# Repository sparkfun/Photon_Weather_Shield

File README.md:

⛔️ Discontinued
====================
*This product has been retired from our catalog.*

SparkFun_Photon_Weather_Shield
===========================

[*Photon Weather Shield (DEV-13630 )*](https://www.sparkfun.com/products/13630)

The SparkFun Photon Weather Shield is an easy to use add-on board for the Photon form Particle.io, which  grants you access to barometric pressure, relative humidity, and temperature. There are also connections on this shield to optional sensors such as wind speed, direction, rain gauge and soil readings!

Repository Contents
-------------------

* **/Firmware** - Necessary libraies and example sketches to use the weather shield. 
* **/Hardware** - All Eagle design files (.brd, .sch)
* **/Production** - Test bed files and production panel files

Documentation
--------------
* **[Hookup Guide](https://learn.sparkfun.com/tutorials/photon-weather-shield-hookup-guide)** - Complete hookup guide for the Photon Wetaher Shield.
* **[SparkFun Fritzing repo](https://github.com/sparkfun/Fritzing_Parts)** - Fritzing diagrams for SparkFun products.
* **[SparkFun 3D Model repo](https://github.com/sparkfun/3D_Models)** - 3D models of SparkFun products. 

Product Versions
----------------
* [DEV-13630](https://www.sparkfun.com/products/13630)- Hardware version 1.0

Version History
---------------

License Information
-------------------

This product is _**open source**_! 

Please review the LICENSE.md file for license information. 

If you have any questions or concerns on licensing, please contact techsupport@sparkfun.com.

Distributed as-is; no warranty is given.

- Your friends at SparkFun.

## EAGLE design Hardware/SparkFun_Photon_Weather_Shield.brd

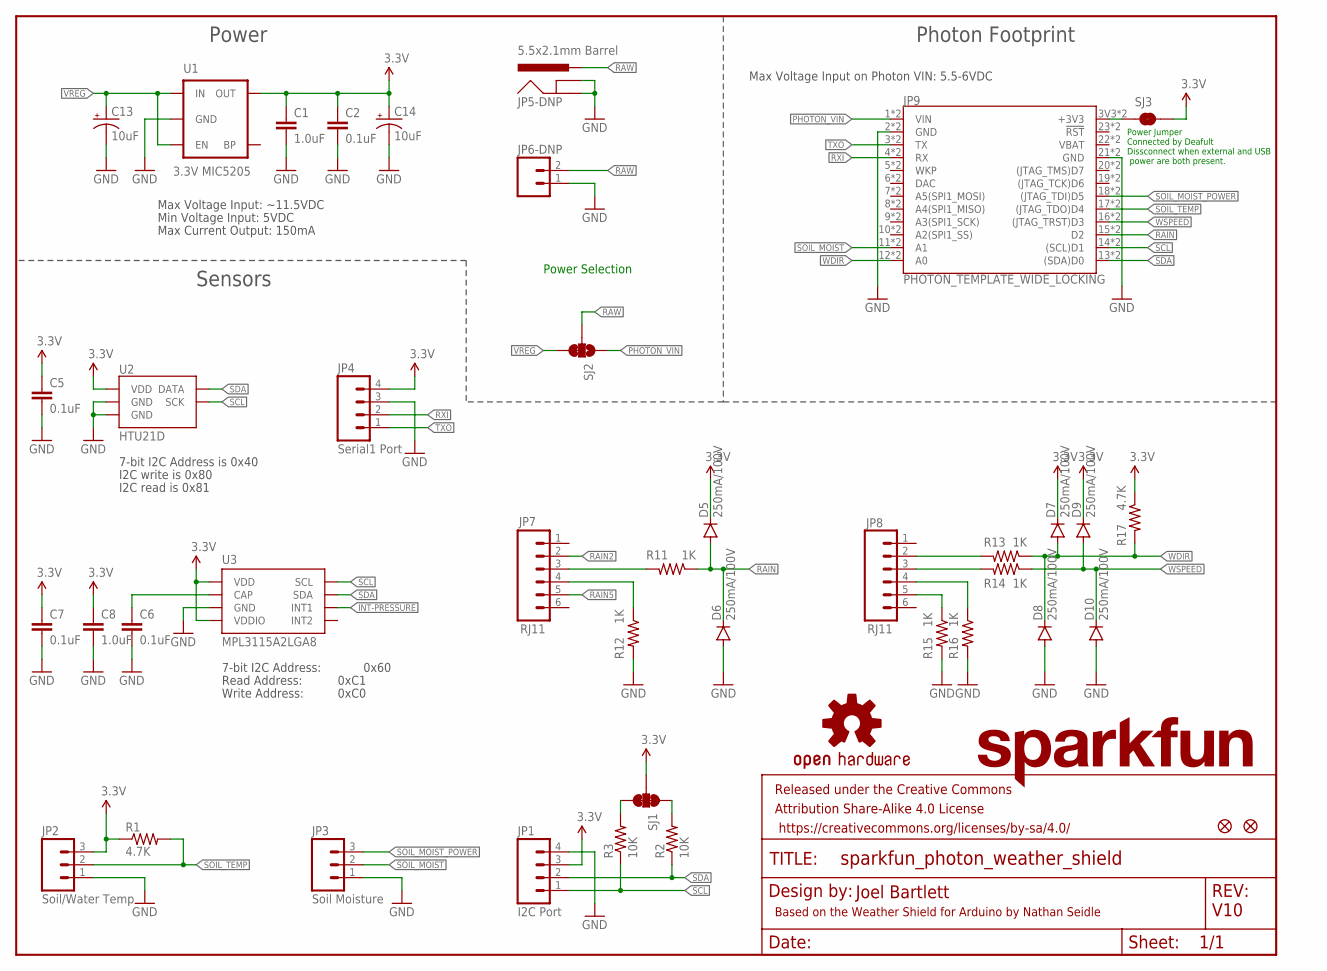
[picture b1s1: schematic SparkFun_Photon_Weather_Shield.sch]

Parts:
C1, C8: 1.0uF; 0603-CAP
C2, C5, C6, C7: 0.1uF; 0603-CAP
C13, C14: 10uF; EIA3216
D5, D6, D7, D8, D9, D10: 250mA/100V; SOD-323
FID1, FID2: FIDUCIAL1X2; FIDUCIAL-1X2
FRAME1: FRAME-LETTER; CREATIVE_COMMONS
JP1: I2C Port; 1X04
JP2: Soil/Water Temp; 1X03
JP3: Soil Moisture; 1X03
JP4: Serial1 Port; 1X04
JP5-DNP: 5.5x2.1mm Barrel; POWER_JACK_SMD
JP6-DNP: M023.5MM; SCREWTERMINAL-3.5MM-2
JP7, JP8: RJ11; RJ11-6
JP9: PHOTON_TEMPLATE_WIDE_LOCKING; SPARK_PHOTON_TEMPLATE_WIDE_LOCKING
LOGO1: OSHW-LOGOM; OSHW-LOGO-M
LOGO2: SFE_LOGO_NAME.1_INCH; SFE_LOGO_NAME_.1
R1, R17: 4.7K; 0603-RES
R2, R3: 10K; 0603-RES
R11, R12, R13, R14, R15, R16: 1K; 0603-RES
SJ1: JUMPER-PAD-3-NC_BY_TRACE; PAD-JUMPER-3-3OF3_NC_BY_TRACE_YES_SILK_FULL_BOX
SJ2: JUMPER-PAD-3-2OF3_NC_BY_TRACE_SMALL; PAD-JUMPER-3-2OF3_NC_BY_TRACE_YES_SILK_FULL_BOX
SJ3: JUMPER-PAD-2-NC_BY_TRACE; PAD-JUMPER-2-NC_BY_TRACE_YES_SILK
U1: 3.3V MIC5205; SOT23-5
U2: HTU21D
U3: MPL3115A2LGA8; LGA8

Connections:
3.3V: C1.1, C2.1, C5.1, C7.1, C8.1, C14.A (+), D5.C, D7.C, D9.C, JP1.3, JP2.3, JP4.4, R1.1, R17.1, SJ1.2, SJ3.2, U1.5 (OUT), U2.VDD, U3.1 (VDD), U3.4 (VDDIO)
GND: C1.2, C2.2, C5.2, C6.2, C7.2, C8.2, C13.C (-), C14.C (-), D6.A, D8.A, D10.A, JP1.4, JP2.1, JP3.1, JP4.3, JP5-DNP.GND (GNDBREAK), JP5-DNP.P$4 (GND), JP6-DNP.1, JP9.2 (GND), JP9.21 (GND), JP9.GND@0 (GND), JP9.GND@2 (GND), R12.2, R15.2, R16.2, U1.2 (GND), U2.7 (GND), U2.GND, U3.3 (GND)
INT-PRESSURE: U3.6 (INT1)
unnamed: JP8.3, R14.2
unnamed: JP8.2, R13.2
unnamed: R3.2, SJ1.3
unnamed: JP7.3, R11.2
unnamed: C6.1, U3.2 (CAP)
unnamed: R2.2, SJ1.1
unnamed: JP9.3V3 (+3V3), JP9.24 (+3V3), SJ3.1
unnamed: JP7.4, R12.1
unnamed: JP8.5, R15.1
unnamed: JP8.4, R16.1
PHOTON_VIN: JP9.1 (VIN), JP9.VIN, SJ2.1
RAIN: D5.A, D6.C, JP9.15 (D2), JP9.D2, R11.1
RAIN2: JP7.2
RAIN5: JP7.5
RAW: JP5-DNP.VIN0 (PWR), JP6-DNP.2, SJ2.2
RXI: JP4.2, JP9.4 (RX), JP9.RX
SCL: JP1.1, JP9.14 ((SCL)D1), JP9.D1 ((SCL)D1), R3.1, U2.SCK, U3.8 (SCL)
SDA: JP1.2, JP9.13 ((SDA)D0), JP9.D0 ((SDA)D0), R2.1, U2.DATA, U3.7 (SDA)
SOIL_MOIST: JP3.2, JP9.11 (A1), JP9.A1
SOIL_MOIST_POWER: JP3.3, JP9.18 ((JTAG_TDI)D5), JP9.D5 ((JTAG_TDI)D5)
SOIL_TEMP: JP2.2, JP9.17 ((JTAG_TDO)D4), JP9.D4 ((JTAG_TDO)D4), R1.2
TXO: JP4.1, JP9.3 (TX), JP9.TX
VREG: C13.A (+), SJ2.3, U1.1 (IN), U1.3 (EN)
WDIR: D7.A, D8.C, JP9.12 (A0), JP9.A0, R13.1, R17.2
WSPEED: D9.A, D10.C, JP9.16 ((JTAG_TRST)D3), JP9.D3 ((JTAG_TRST)D3), R14.1

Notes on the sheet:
Max Voltage Input: ~11.5VDC
Max Current Output: 150mA
Read Address:
Write Address:
7-bit I2C Address:
0x60
0xC1
0xC0
7-bit I2C Address is 0x40
I2C write is 0x80
I2C read is 0x81
Sensors
Power
Photon Footprint
Power Selection
Based on the Weather Shield for Arduino by Nathan Seidle
Min Voltage Input: 5VDC
Power Jumper Connected by Deafult Dissconnect when external and USB power are both present.
Joel Bartlett
V10
Max Voltage Input on Photon VIN: 5.5-6VDC

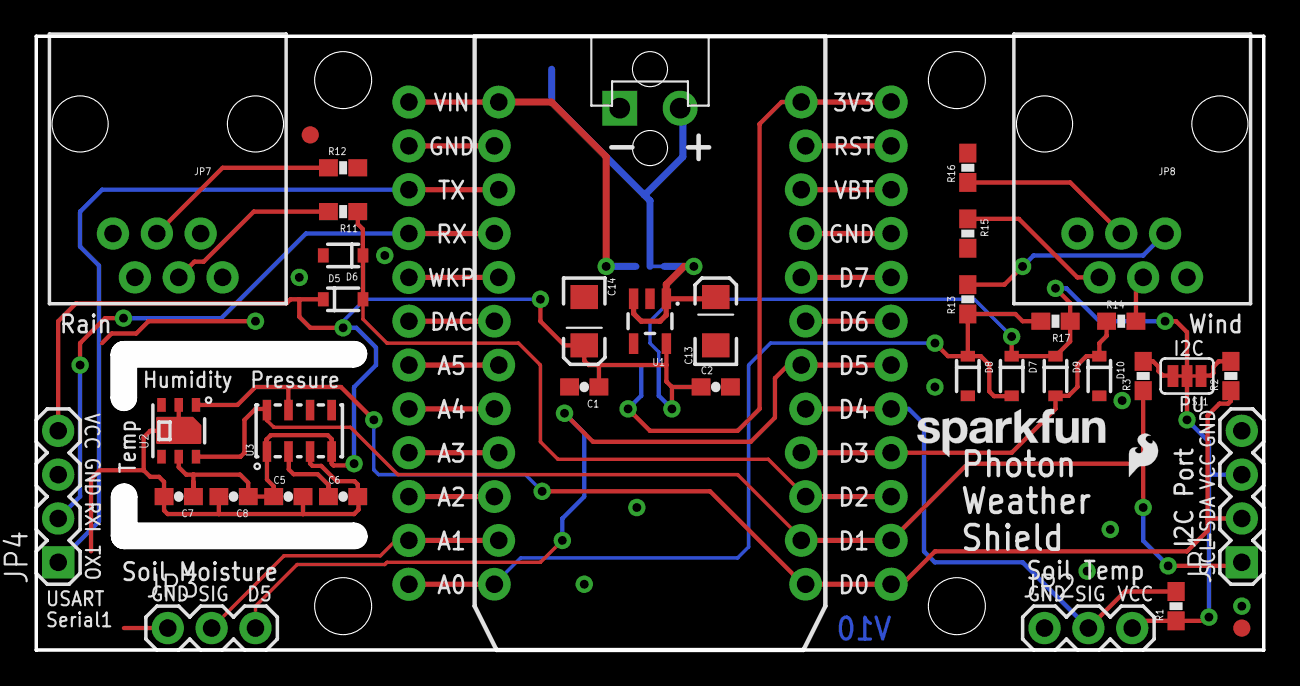
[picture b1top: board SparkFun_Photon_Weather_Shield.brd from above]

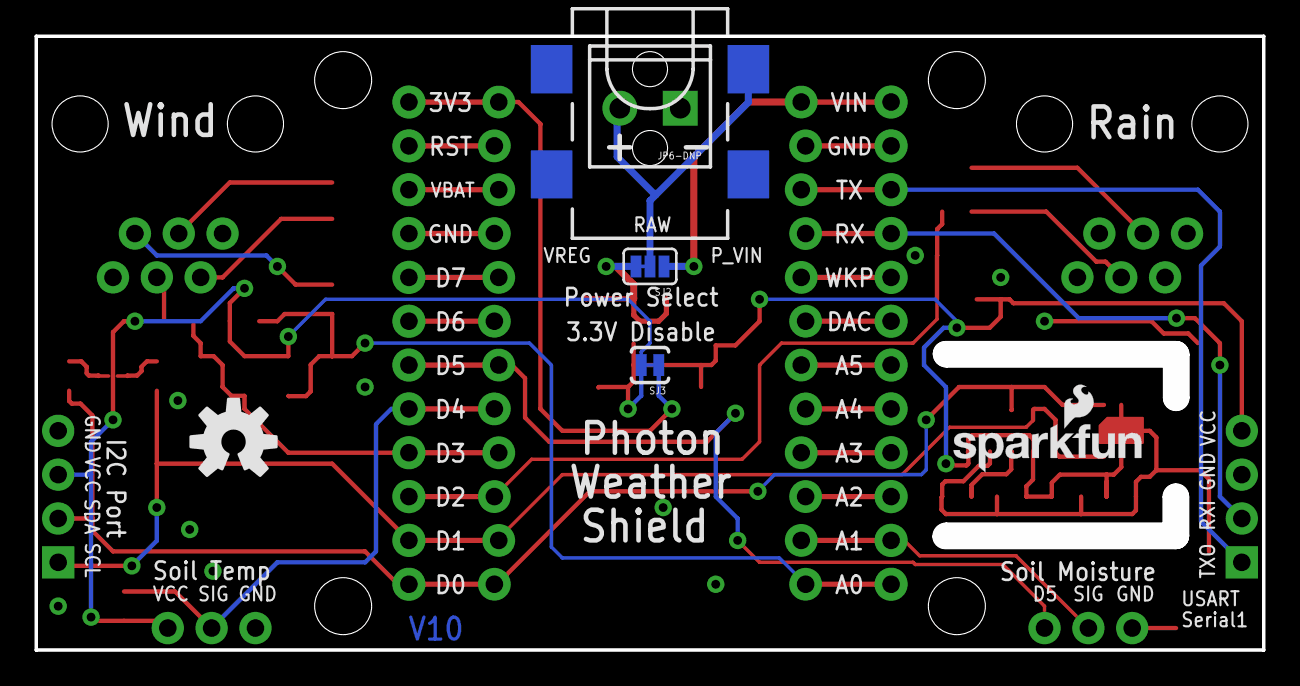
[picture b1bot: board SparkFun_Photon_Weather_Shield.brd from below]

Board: 2 copper layers, 69.8 x 34.2 mm, 46 parts (6 on the bottom side), 25 nets.

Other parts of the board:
U$1: SFE_LOGO_NAME_FLAME_.1
U$3: SFE_LOGO_FLAME_.1

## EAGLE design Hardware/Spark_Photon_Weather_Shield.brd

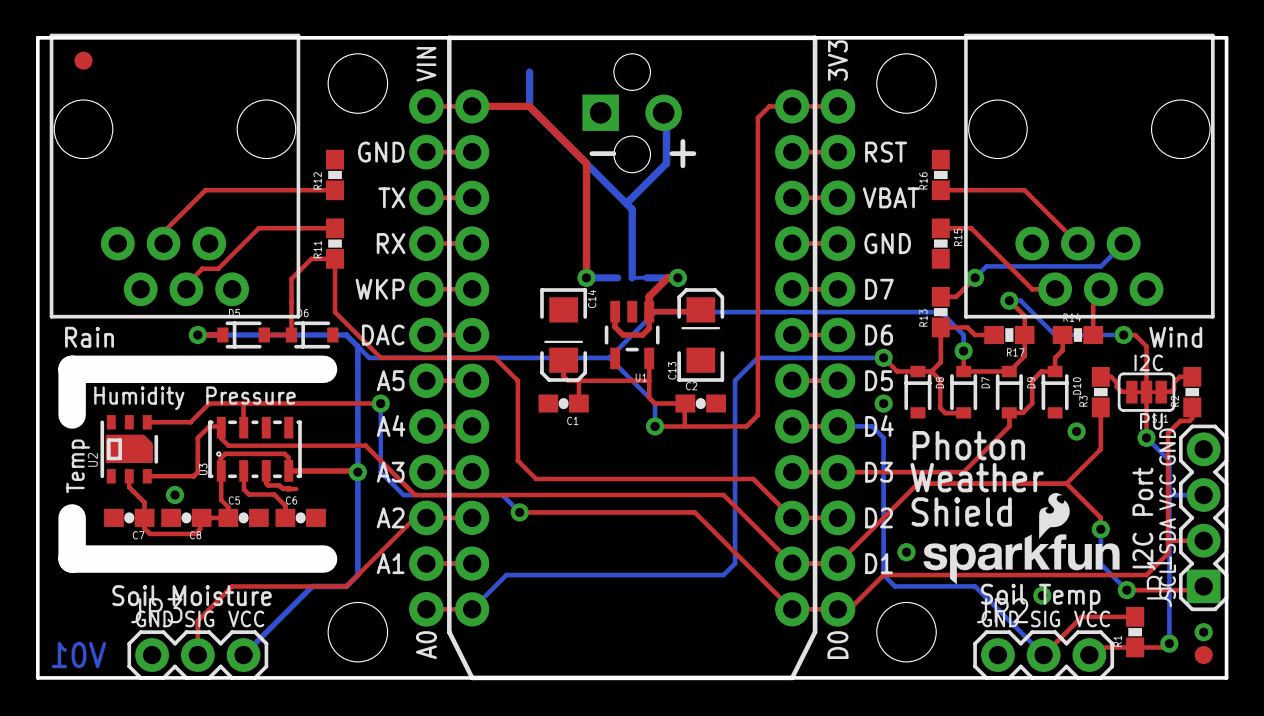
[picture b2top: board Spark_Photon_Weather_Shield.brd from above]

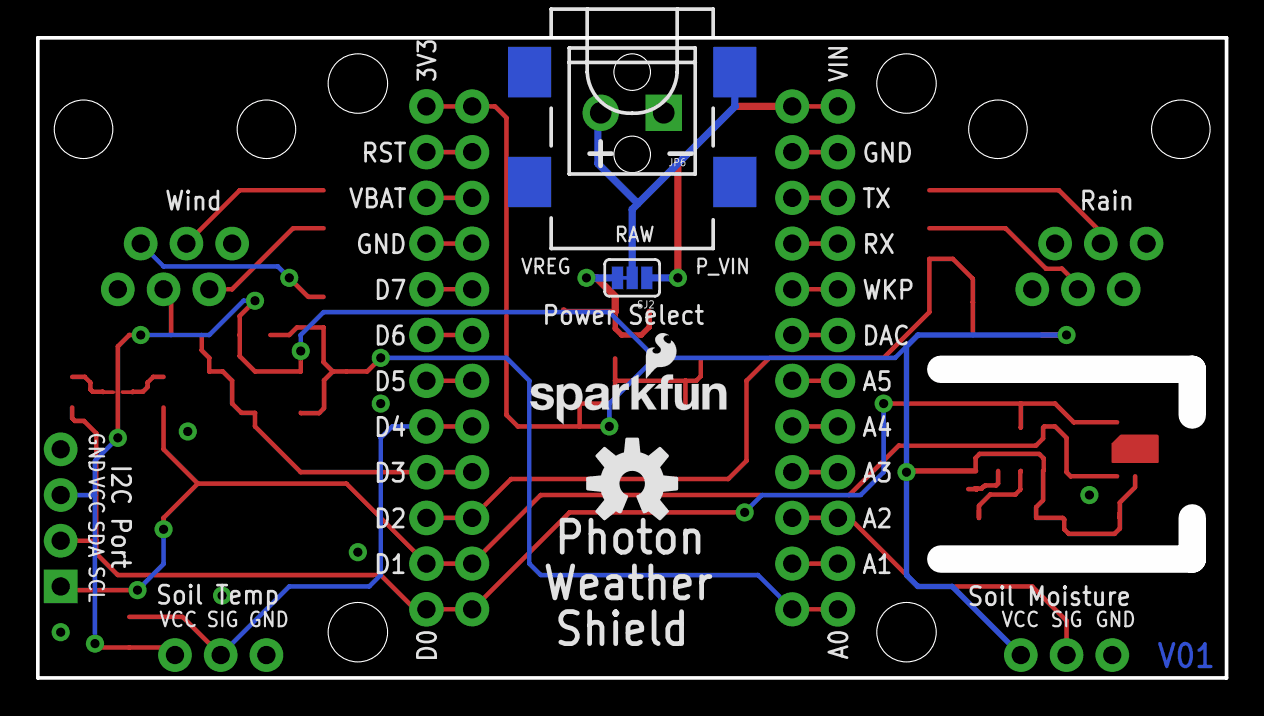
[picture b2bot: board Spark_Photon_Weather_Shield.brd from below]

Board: 2 copper layers, 64.7 x 34.2 mm, 43 parts (5 on the bottom side), 24 nets.

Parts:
C1, C8: 1uF; 0603-CAP
C2, C5, C6, C7: 0.1uF; 0603-CAP
C13, C14: 10uF; EIA3216
D5, D6, D7, D8, D9, D10: BAS16; SOD-323
FID1, FID2: FIDUCIAL1X2; FIDUCIAL-1X2
FRAME2: CREATIVE_COMMONS
JP1: 1X04
JP2, JP3: 1X03
JP4: SPARK_PHOTONTEMPLATE; SPARK_PHOTON_TEMPLATE
JP5: 5.5x2.1mm Barrel; POWER_JACK_SMD
JP6: M023.5MM; SCREWTERMINAL-3.5MM-2
JP7-DNP: RJ11-RAIN; RJ11-6
JP8-DNP: RJ11-WIND; RJ11-6
LOGO1: OSHW-LOGOM; OSHW-LOGO-M
LOGO2: SFE_LOGO_NAME_FLAME.1_INCH; SFE_LOGO_NAME_FLAME_.1
R1, R17: 4.7K; 0603-RES
R2, R3: 10K; 0603-RES
R11, R12, R13, R14, R15, R16: 1K; 0603-RES
SJ1: PAD-JUMPER-3-3OF3_NC_BY_TRACE_YES_SILK_FULL_BOX
SJ2: PAD-JUMPER-3-2OF3_NC_BY_TRACE_YES_SILK_FULL_BOX
U1: 3.3V MIC5219; SOT23-5
U2: HTU21D
U3: MPL3115A2LGA8; LGA8
U$1: SFE_LOGO_NAME_FLAME_.1

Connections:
3.3V: C1.1, C2.1, C5.1, C7.1, C8.1, C14.A, D5.1, D7.1, D9.1, JP1.3, JP2.3, JP3.3, JP4.3V3, JP4.24, R1.1, R17.1, SJ1.2, U1.5, U2.VDD, U3.1, U3.4
GND: C1.2, C2.2, C5.2, C6.2, C7.2, C8.2, C13.C, C14.C, D6.2, D8.2, D10.2, JP1.4, JP2.1, JP3.1, JP4.2, JP4.21, JP4.GND@0, JP4.GND@2, JP5.GND, JP5.P$4, JP6.1, R12.2, R15.2, R16.2, U1.2, U2.7, U2.GND, U3.3
LIGHT: JP4.11, JP4.A1
unnamed: JP8-DNP.3, R14.2
unnamed: JP8-DNP.2, R13.2
unnamed: R3.2, SJ1.3
unnamed: JP7-DNP.3, R11.2
unnamed: C6.1, U3.2
unnamed: R2.2, SJ1.1
unnamed: JP7-DNP.4, R12.1
unnamed: JP8-DNP.5, R15.1
unnamed: JP8-DNP.4, R16.1
PHOTON_VIN: JP4.1, JP4.VIN, SJ2.1
RAIN: D5.2, D6.1, JP4.15, JP4.D2, R11.1
RAW: JP5.VIN0, JP6.2, SJ2.2
RXI: JP4.4, JP4.RX
SCL: JP1.1, JP4.14, JP4.D1, R3.1, U2.SCK, U3.8
SDA: JP1.2, JP4.13, JP4.D0, R2.1, U2.DATA, U3.7
SOIL_MOIST: JP3.2, JP4.10, JP4.A2
SOIL_TEMP: JP2.2, JP4.17, JP4.D4, R1.2
TXO: JP4.3, JP4.TX
VREG: C13.A, SJ2.3, U1.1, U1.3
WDIR: D7.2, D8.1, JP4.12, JP4.A0, R13.1, R17.2
WSPEED: D9.2, D10.1, JP4.16, JP4.D3, R14.1

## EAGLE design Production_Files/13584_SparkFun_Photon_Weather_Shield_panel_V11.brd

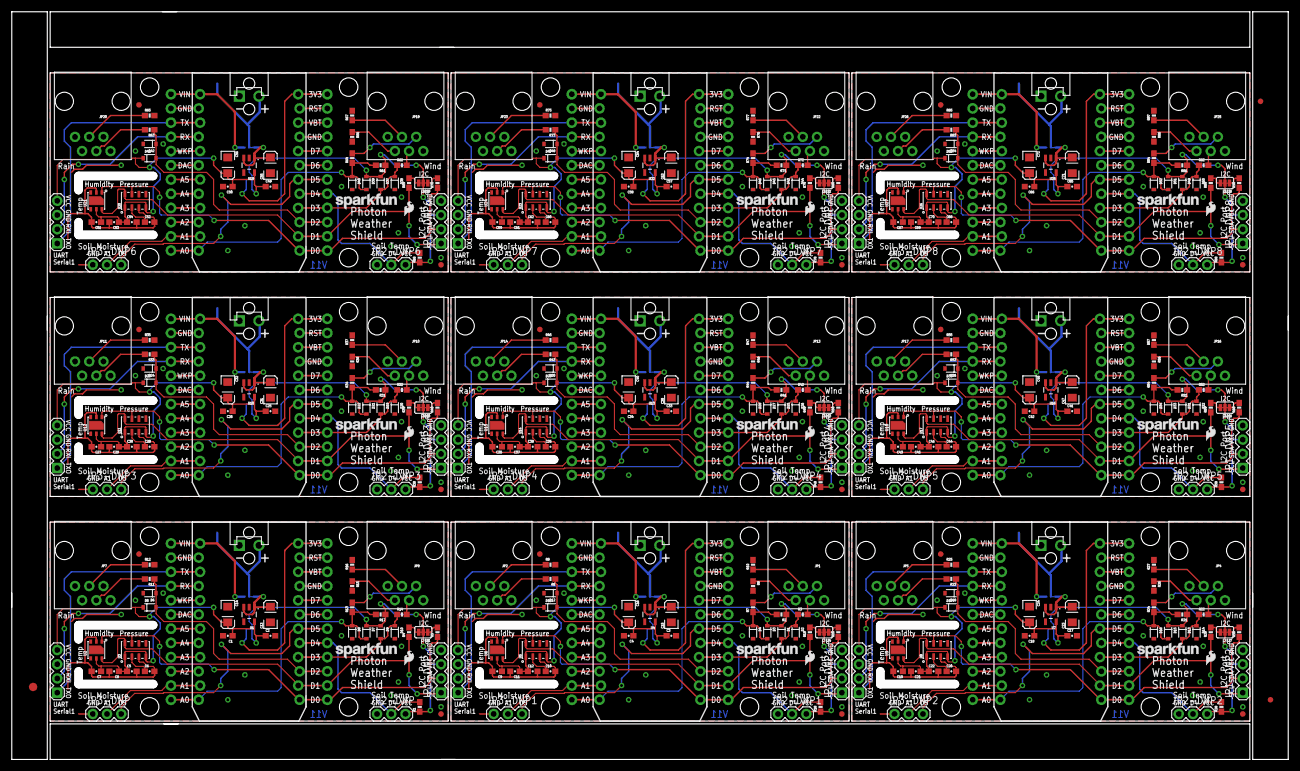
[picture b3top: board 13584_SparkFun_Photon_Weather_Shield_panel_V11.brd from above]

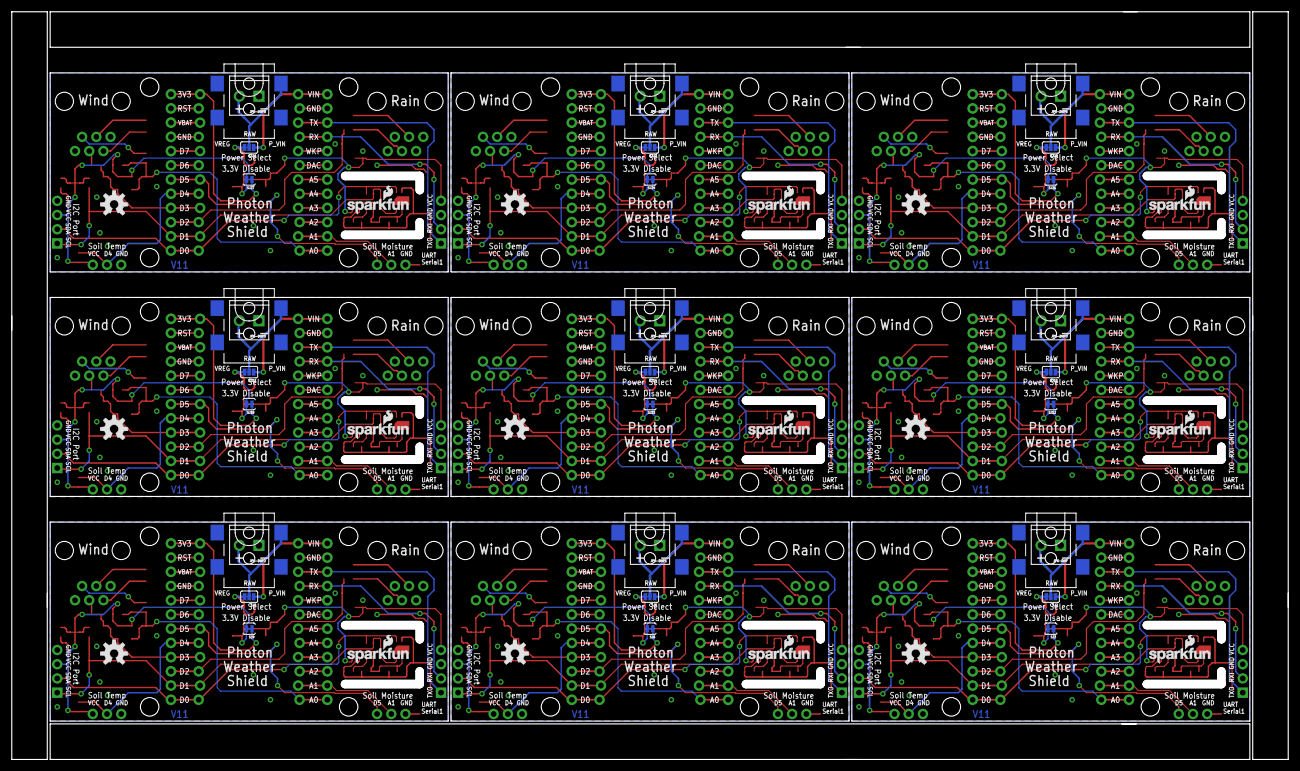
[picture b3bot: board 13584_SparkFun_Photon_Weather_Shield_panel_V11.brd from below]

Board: 2 copper layers, 226.8 x 132.3 mm, 408 parts (54 on the bottom side), 225 nets.

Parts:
C1, C4, C8, C11, C18, C21, C26, C29, C34, C37, C42, C45, C50, C53, C58, C61, C66, C69: 1.0uF; 0603-CAP
C2, C3, C5, C6, C7, C9, C10, C12, C17, C19, C20, C22, C25, C27, C28, C30, C33, C35, C36, C38, C41, C43, C44, C46, C49, C51, C52, C54, C57, C59, C60, C62, C65, C67, C68, C70: 0.1uF; 0603-CAP
C13, C14, C15, C16, C23, C24, C31, C32, C39, C40, C47, C48, C55, C56, C63, C64, C71, C72: 10uF; EIA3216
D1, D2, D3, D4, D5, D6, D7, D8, D9, D10, D11, D12, D13, D14, D15, D16, D17, D18, D19, D20, D21, D22, D23, D24, D25, D26, D27, D28, D29, D30, D31, D32, D33, D34, D35, D36, D37, D38, D39, D40, D41, D42, D43, D44, D45, D46, D47, D48, D49, D50, D51, D52, D53, D54: 250mA/100V; SOD-323
E$1: FIDUCIAL-1.5X3
E$7, E$8: FIDUCIAL-1X2
FID1, FID2, FID3, FID4, FID5, FID6, FID7, FID8, FID9, FID10, FID11, FID12, FID13, FID14, FID15, FID16, FID17, FID18: FIDUCIAL1X2; FIDUCIAL-1X2
JP1, JP2, JP4, JP5, JP7, JP8, JP10, JP11, JP13, JP14, JP16, JP17, JP19, JP20, JP22, JP23, JP25, JP26: RJ11; RJ11-6
JP1-DNP, JP1-DNP1, JP1-DNP2, JP1-DNP3, JP1-DNP4, JP1-DNP5, JP1-DNP6, JP1-DNP7, JP1-DNP8: I2C Port; 1X04
JP2-DNP, JP2-DNP1, JP2-DNP2, JP2-DNP3, JP2-DNP4, JP2-DNP5, JP2-DNP6, JP2-DNP7, JP2-DNP8: Soil/Water Temp; 1X03
JP3, JP6, JP9, JP12, JP15, JP18, JP21, JP24, JP27: PHOTON_TEMPLATE_WIDE_LOCKING; SPARK_PHOTON_TEMPLATE_WIDE_LOCKING
JP3-DNP, JP3-DNP1, JP3-DNP2, JP3-DNP3, JP3-DNP4, JP3-DNP5, JP3-DNP6, JP3-DNP7, JP3-DNP8: Soil Moisture; 1X03
JP4-DNP, JP4-DNP1, JP4-DNP2, JP4-DNP3, JP4-DNP4, JP4-DNP5, JP4-DNP6, JP4-DNP7, JP4-DNP8: Serial1 Port; 1X04
JP5-DNP, JP5-DNP1, JP5-DNP2, JP5-DNP3, JP5-DNP4, JP5-DNP5, JP5-DNP6, JP5-DNP7, JP5-DNP8: 5.5x2.1mm Barrel; POWER_JACK_SMD
JP6-DNP, JP6-DNP1, JP6-DNP2, JP6-DNP3, JP6-DNP4, JP6-DNP5, JP6-DNP6, JP6-DNP7, JP6-DNP8: SCREWTERMINAL-3.5MM-2
LOGO1, LOGO3, LOGO5, LOGO7, LOGO9, LOGO11, LOGO13, LOGO15, LOGO17: OSHW-LOGOM; OSHW-LOGO-M
LOGO2, LOGO4, LOGO6, LOGO8, LOGO10, LOGO12, LOGO14, LOGO16, LOGO18: SFE_LOGO_NAME.1_INCH; SFE_LOGO_NAME_.1
R1, R2, R4, R5, R17, R18, R19, R20, R21, R28, R29, R30, R31, R38, R39, R40, R41, R48, R49, R50, R51, R58, R59, R60, R61, R68, R69, R70, R71, R78, R79, R80, R81, R88, R89, R90: 4.7K; 0603-RES
R3, R6, R7, R8, R9, R10, R11, R12, R13, R14, R15, R16, R22, R23, R24, R25, R26, R27, R32, R33, R34, R35, R36, R37, R42, R43, R44, R45, R46, R47, R52, R53, R54, R55, R56, R57, R62, R63, R64, R65, R66, R67, R72, R73, R74, R75, R76, R77, R82, R83, R84, R85, R86, R87: 1K; 0603-RES
SJ1, SJ4, SJ7, SJ10, SJ13, SJ16, SJ19, SJ22, SJ25: PAD-JUMPER-3-3OF3_NC_BY_TRACE_YES_SILK_FULL_BOX
SJ2, SJ5, SJ8, SJ11, SJ14, SJ17, SJ20, SJ23, SJ26: PAD-JUMPER-3-2OF3_NC_BY_TRACE_YES_SILK_FULL_BOX
SJ3, SJ6, SJ9, SJ12, SJ15, SJ18, SJ21, SJ24, SJ27: PAD-JUMPER-2-NC_BY_TRACE_YES_SILK
U1, U4, U7, U10, U13, U16, U19, U22, U25: 3.3V MIC5219; SOT23-5
U2, U6, U9, U12, U15, U18, U21, U24, U27: SI7021
U3, U5, U8, U11, U14, U17, U20, U23, U26: MPL3115A2LGA8; LGA8
U$1, U$2, U$5, U$7, U$9, U$11, U$13, U$15, U$17: SFE_LOGO_NAME_FLAME_.1
U$3, U$4, U$6, U$8, U$10, U$12, U$14, U$16, U$18: SFE_LOGO_FLAME_.1

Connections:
3.3V: C1.1, C2.1, C5.1, C7.1, C8.1, C14.A, D5.C, D7.C, D9.C, JP1-DNP.3, JP2-DNP.3, JP4-DNP.4, R1.1, R17.1, SJ1.2, SJ3.2, U1.5, U2.VDD, U3.1, U3.4
3.3V1: C3.1, C4.1, C9.1, C11.1, C12.1, C16.A, D1.C, D3.C, D11.C, JP1-DNP1.3, JP2-DNP1.3, JP4-DNP1.4, R2.1, R18.1, SJ4.2, SJ6.2, U4.5, U5.1, U5.4, U6.VDD
3.3V2: C17.1, C18.1, C19.1, C21.1, C22.1, C24.A, D13.C, D15.C, D17.C, JP1-DNP2.3, JP2-DNP2.3, JP4-DNP2.4, R21.1, R28.1, SJ7.2, SJ9.2, U7.5, U8.1, U8.4, U9.VDD
3.3V3: C25.1, C26.1, C27.1, C29.1, C30.1, C32.A, D19.C, D21.C, D23.C, JP1-DNP3.3, JP2-DNP3.3, JP4-DNP3.4, R31.1, R38.1, SJ10.2, SJ12.2, U10.5, U11.1, U11.4, U12.VDD
3.3V4: C33.1, C34.1, C35.1, C37.1, C38.1, C40.A, D25.C, D27.C, D29.C, JP1-DNP4.3, JP2-DNP4.3, JP4-DNP4.4, R41.1, R48.1, SJ13.2, SJ15.2, U13.5, U14.1, U14.4, U15.VDD
3.3V5: C41.1, C42.1, C43.1, C45.1, C46.1, C48.A, D31.C, D33.C, D35.C, JP1-DNP5.3, JP2-DNP5.3, JP4-DNP5.4, R51.1, R58.1, SJ16.2, SJ18.2, U16.5, U17.1, U17.4, U18.VDD
3.3V6: C49.1, C50.1, C51.1, C53.1, C54.1, C56.A, D37.C, D39.C, D41.C, JP1-DNP6.3, JP2-DNP6.3, JP4-DNP6.4, R61.1, R68.1, SJ19.2, SJ21.2, U19.5, U20.1, U20.4, U21.VDD
3.3V7: C57.1, C58.1, C59.1, C61.1, C62.1, C64.A, D43.C, D45.C, D47.C, JP1-DNP7.3, JP2-DNP7.3, JP4-DNP7.4, R71.1, R78.1, SJ22.2, SJ24.2, U22.5, U23.1, U23.4, U24.VDD
3.3V8: C65.1, C66.1, C67.1, C69.1, C70.1, C72.A, D49.C, D51.C, D53.C, JP1-DNP8.3, JP2-DNP8.3, JP4-DNP8.4, R81.1, R88.1, SJ25.2, SJ27.2, U25.5, U26.1, U26.4, U27.VDD
GND: C1.2, C2.2, C5.2, C6.2, C7.2, C8.2, C13.C, C14.C, D6.A, D8.A, D10.A, JP1-DNP.4, JP2-DNP.1, JP3-DNP.1, JP4-DNP.3, JP5-DNP.GND, JP5-DNP.P$4, JP6-DNP.1, JP9.2, JP9.21, JP9.GND@0, JP9.GND@2, R12.2, R15.2, R16.2, U1.2, U2.GND, U3.3
GND1: C3.2, C4.2, C9.2, C10.2, C11.2, C12.2, C15.C, C16.C, D2.A, D4.A, D12.A, JP1-DNP1.4, JP2-DNP1.1, JP3.2, JP3.21, JP3.GND@0, JP3.GND@2, JP3-DNP1.1, JP4-DNP1.3, JP5-DNP1.GND, JP5-DNP1.P$4, JP6-DNP1.1, R8.2, R9.2, R10.2, U4.2, U5.3, U6.GND
GND2: C17.2, C18.2, C19.2, C20.2, C21.2, C22.2, C23.C, C24.C, D14.A, D16.A, D18.A, JP1-DNP2.4, JP2-DNP2.1, JP3-DNP2.1, JP4-DNP2.3, JP5-DNP2.GND, JP5-DNP2.P$4, JP6.2, JP6.21, JP6.GND@0, JP6.GND@2, JP6-DNP2.1, R25.2, R26.2, R27.2, U7.2, U8.3, U9.GND
GND3: C25.2, C26.2, C27.2, C28.2, C29.2, C30.2, C31.C, C32.C, D20.A, D22.A, D24.A, JP1-DNP3.4, JP2-DNP3.1, JP3-DNP3.1, JP4-DNP3.3, JP5-DNP3.GND, JP5-DNP3.P$4, JP6-DNP3.1, JP12.2, JP12.21, JP12.GND@0, JP12.GND@2, R35.2, R36.2, R37.2, U10.2, U11.3, U12.GND
GND4: C33.2, C34.2, C35.2, C36.2, C37.2, C38.2, C39.C, C40.C, D26.A, D28.A, D30.A, JP1-DNP4.4, JP2-DNP4.1, JP3-DNP4.1, JP4-DNP4.3, JP5-DNP4.GND, JP5-DNP4.P$4, JP6-DNP4.1, JP15.2, JP15.21, JP15.GND@0, JP15.GND@2, R45.2, R46.2, R47.2, U13.2, U14.3, U15.GND
GND5: C41.2, C42.2, C43.2, C44.2, C45.2, C46.2, C47.C, C48.C, D32.A, D34.A, D36.A, JP1-DNP5.4, JP2-DNP5.1, JP3-DNP5.1, JP4-DNP5.3, JP5-DNP5.GND, JP5-DNP5.P$4, JP6-DNP5.1, JP18.2, JP18.21, JP18.GND@0, JP18.GND@2, R55.2, R56.2, R57.2, U16.2, U17.3, U18.GND
GND6: C49.2, C50.2, C51.2, C52.2, C53.2, C54.2, C55.C, C56.C, D38.A, D40.A, D42.A, JP1-DNP6.4, JP2-DNP6.1, JP3-DNP6.1, JP4-DNP6.3, JP5-DNP6.GND, JP5-DNP6.P$4, JP6-DNP6.1, JP21.2, JP21.21, JP21.GND@0, JP21.GND@2, R65.2, R66.2, R67.2, U19.2, U20.3, U21.GND
GND7: C57.2, C58.2, C59.2, C60.2, C61.2, C62.2, C63.C, C64.C, D44.A, D46.A, D48.A, JP1-DNP7.4, JP2-DNP7.1, JP3-DNP7.1, JP4-DNP7.3, JP5-DNP7.GND, JP5-DNP7.P$4, JP6-DNP7.1, JP24.2, JP24.21, JP24.GND@0, JP24.GND@2, R75.2, R76.2, R77.2, U22.2, U23.3, U24.GND
GND8: C65.2, C66.2, C67.2, C68.2, C69.2, C70.2, C71.C, C72.C, D50.A, D52.A, D54.A, JP1-DNP8.4, JP2-DNP8.1, JP3-DNP8.1, JP4-DNP8.3, JP5-DNP8.GND, JP5-DNP8.P$4, JP6-DNP8.1, JP27.2, JP27.21, JP27.GND@0, JP27.GND@2, R85.2, R86.2, R87.2, U25.2, U26.3, U27.GND
unnamed: JP8.3, R14.2
unnamed: JP8.2, R13.2
unnamed: R4.2, SJ1.3
unnamed: JP7.3, R11.2
unnamed: C6.1, U3.2
unnamed: R5.2, SJ1.1
unnamed: JP9.3V3, JP9.24, SJ3.1
unnamed: C10.1, U5.2
unnamed: JP1.2, R7.2
unnamed: JP1.3, R3.2
unnamed: JP7.4, R12.1
unnamed: JP8.5, R15.1
unnamed: JP8.4, R16.1
unnamed: JP2.3, R6.2
unnamed: JP2.4, R8.1
unnamed: JP1.5, R9.1
unnamed: JP1.4, R10.1
unnamed: R19.2, SJ4.3
unnamed: R20.2, SJ4.1
unnamed: JP3.3V3, JP3.24, SJ6.1
unnamed: C20.1, U8.2
unnamed: JP4.2, R24.2
unnamed: JP4.3, R22.2
unnamed: JP5.3, R23.2
unnamed: JP5.4, R25.1
unnamed: JP4.5, R26.1
unnamed: JP4.4, R27.1
unnamed: R29.2, SJ7.3
unnamed: R30.2, SJ7.1
unnamed: JP6.3V3, JP6.24, SJ9.1
unnamed: C28.1, U11.2
unnamed: JP10.2, R34.2
unnamed: JP10.3, R32.2
unnamed: JP11.3, R33.2
unnamed: JP11.4, R35.1
unnamed: JP10.5, R36.1
unnamed: JP10.4, R37.1
unnamed: R39.2, SJ10.3
unnamed: R40.2, SJ10.1
unnamed: JP12.3V3, JP12.24, SJ12.1
unnamed: C36.1, U14.2
unnamed: JP13.2, R44.2
unnamed: JP13.3, R42.2
unnamed: JP14.3, R43.2
unnamed: JP14.4, R45.1
unnamed: JP13.5, R46.1
unnamed: JP13.4, R47.1
unnamed: R49.2, SJ13.3
unnamed: R50.2, SJ13.1
unnamed: JP15.3V3, JP15.24, SJ15.1
unnamed: C44.1, U17.2
unnamed: JP16.2, R54.2
unnamed: JP16.3, R52.2
unnamed: JP17.3, R53.2
unnamed: JP17.4, R55.1
unnamed: JP16.5, R56.1
unnamed: JP16.4, R57.1
unnamed: R59.2, SJ16.3
unnamed: R60.2, SJ16.1
unnamed: JP18.3V3, JP18.24, SJ18.1
unnamed: C52.1, U20.2
unnamed: JP19.2, R64.2
unnamed: JP19.3, R62.2
unnamed: JP20.3, R63.2
unnamed: JP20.4, R65.1
unnamed: JP19.5, R66.1
unnamed: JP19.4, R67.1
unnamed: R69.2, SJ19.3
unnamed: R70.2, SJ19.1
unnamed: JP21.3V3, JP21.24, SJ21.1
unnamed: C60.1, U23.2
unnamed: JP22.2, R74.2
unnamed: JP22.3, R72.2
unnamed: JP23.3, R73.2
unnamed: JP23.4, R75.1
unnamed: JP22.5, R76.1
unnamed: JP22.4, R77.1
unnamed: R79.2, SJ22.3
unnamed: R80.2, SJ22.1
unnamed: JP24.3V3, JP24.24, SJ24.1
unnamed: C68.1, U26.2
unnamed: JP25.2, R84.2
unnamed: JP25.3, R82.2
unnamed: JP26.3, R83.2
unnamed: JP26.4, R85.1
unnamed: JP25.5, R86.1
unnamed: JP25.4, R87.1
unnamed: R89.2, SJ25.3
unnamed: R90.2, SJ25.1
unnamed: JP27.3V3, JP27.24, SJ27.1
PHOTON_VIN: JP9.1, JP9.VIN, SJ2.1
PHOTON_VIN1: JP3.1, JP3.VIN, SJ5.1
PHOTON_VIN2: JP6.1, JP6.VIN, SJ8.1
PHOTON_VIN3: JP12.1, JP12.VIN, SJ11.1
PHOTON_VIN4: JP15.1, JP15.VIN, SJ14.1
PHOTON_VIN5: JP18.1, JP18.VIN, SJ17.1
PHOTON_VIN6: JP21.1, JP21.VIN, SJ20.1
PHOTON_VIN7: JP24.1, JP24.VIN, SJ23.1
PHOTON_VIN8: JP27.1, JP27.VIN, SJ26.1
RAIN: D5.A, D6.C, JP9.15, JP9.D2, R11.1
RAIN1: D11.A, D12.C, JP3.15, JP3.D2, R6.1
RAIN6: D17.A, D18.C, JP6.15, JP6.D2, R23.1
RAIN9: D23.A, D24.C, JP12.15, JP12.D2, R33.1
RAIN12: D29.A, D30.C, JP15.15, JP15.D2, R43.1
RAIN15: D35.A, D36.C, JP18.15, JP18.D2, R53.1
RAIN18: D41.A, D42.C, JP21.15, JP21.D2, R63.1
RAIN21: D47.A, D48.C, JP24.15, JP24.D2, R73.1
RAIN24: D53.A, D54.C, JP27.15, JP27.D2, R83.1
RAW: JP5-DNP.VIN0, JP6-DNP.2, SJ2.2
RAW1: JP5-DNP1.VIN0, JP6-DNP1.2, SJ5.2
RAW2: JP5-DNP2.VIN0, JP6-DNP2.2, SJ8.2
RAW3: JP5-DNP3.VIN0, JP6-DNP3.2, SJ11.2
RAW4: JP5-DNP4.VIN0, JP6-DNP4.2, SJ14.2
RAW5: JP5-DNP5.VIN0, JP6-DNP5.2, SJ17.2
RAW6: JP5-DNP6.VIN0, JP6-DNP6.2, SJ20.2
RAW7: JP5-DNP7.VIN0, JP6-DNP7.2, SJ23.2
RAW8: JP5-DNP8.VIN0, JP6-DNP8.2, SJ26.2
RXI: JP4-DNP.2, JP9.4, JP9.RX
RXI1: JP3.4, JP3.RX, JP4-DNP1.2
RXI2: JP4-DNP2.2, JP6.4, JP6.RX
RXI3: JP4-DNP3.2, JP12.4, JP12.RX
RXI4: JP4-DNP4.2, JP15.4, JP15.RX
RXI5: JP4-DNP5.2, JP18.4, JP18.RX
RXI6: JP4-DNP6.2, JP21.4, JP21.RX
RXI7: JP4-DNP7.2, JP24.4, JP24.RX
RXI8: JP4-DNP8.2, JP27.4, JP27.RX
SCL: JP1-DNP.1, JP9.14, JP9.D1, R4.1, U2.SCK, U3.8
SCL1: JP1-DNP1.1, JP3.14, JP3.D1, R19.1, U5.8, U6.SCK
SCL2: JP1-DNP2.1, JP6.14, JP6.D1, R29.1, U8.8, U9.SCK
SCL3: JP1-DNP3.1, JP12.14, JP12.D1, R39.1, U11.8, U12.SCK
SCL4: JP1-DNP4.1, JP15.14, JP15.D1, R49.1, U14.8, U15.SCK
SCL5: JP1-DNP5.1, JP18.14, JP18.D1, R59.1, U17.8, U18.SCK
SCL6: JP1-DNP6.1, JP21.14, JP21.D1, R69.1, U20.8, U21.SCK
SCL7: JP1-DNP7.1, JP24.14, JP24.D1, R79.1, U23.8, U24.SCK
SCL8: JP1-DNP8.1, JP27.14, JP27.D1, R89.1, U26.8, U27.SCK
SDA: JP1-DNP.2, JP9.13, JP9.D0, R5.1, U2.DATA, U3.7
SDA1: JP1-DNP1.2, JP3.13, JP3.D0, R20.1, U5.7, U6.DATA
SDA2: JP1-DNP2.2, JP6.13, JP6.D0, R30.1, U8.7, U9.DATA
SDA3: JP1-DNP3.2, JP12.13, JP12.D0, R40.1, U11.7, U12.DATA
SDA4: JP1-DNP4.2, JP15.13, JP15.D0, R50.1, U14.7, U15.DATA
SDA5: JP1-DNP5.2, JP18.13, JP18.D0, R60.1, U17.7, U18.DATA
SDA6: JP1-DNP6.2, JP21.13, JP21.D0, R70.1, U20.7, U21.DATA
SDA7: JP1-DNP7.2, JP24.13, JP24.D0, R80.1, U23.7, U24.DATA
SDA8: JP1-DNP8.2, JP27.13, JP27.D0, R90.1, U26.7, U27.DATA
SOIL_MOIST: JP3-DNP.2, JP9.11, JP9.A1
SOIL_MOIST3: JP3.11, JP3.A1, JP3-DNP1.2
SOIL_MOIST4: JP3-DNP2.2, JP6.11, JP6.A1
SOIL_MOIST5: JP3-DNP3.2, JP12.11, JP12.A1
SOIL_MOIST6: JP3-DNP4.2, JP15.11, JP15.A1
SOIL_MOIST7: JP3-DNP5.2, JP18.11, JP18.A1
SOIL_MOIST8: JP3-DNP6.2, JP21.11, JP21.A1
SOIL_MOIST9: JP3-DNP7.2, JP24.11, JP24.A1
SOIL_MOIST10: JP3-DNP8.2, JP27.11, JP27.A1
SOIL_MOIST_POWER: JP3-DNP.3, JP9.18, JP9.D5
SOIL_MOIST_POWER1: JP3.18, JP3.D5, JP3-DNP1.3
SOIL_MOIST_POWER2: JP3-DNP2.3, JP6.18, JP6.D5
SOIL_MOIST_POWER3: JP3-DNP3.3, JP12.18, JP12.D5
SOIL_MOIST_POWER4: JP3-DNP4.3, JP15.18, JP15.D5
SOIL_MOIST_POWER5: JP3-DNP5.3, JP18.18, JP18.D5
SOIL_MOIST_POWER6: JP3-DNP6.3, JP21.18, JP21.D5
SOIL_MOIST_POWER7: JP3-DNP7.3, JP24.18, JP24.D5
SOIL_MOIST_POWER8: JP3-DNP8.3, JP27.18, JP27.D5
SOIL_TEMP: JP2-DNP.2, JP9.17, JP9.D4, R1.2
SOIL_TEMP2: JP2-DNP1.2, JP3.17, JP3.D4, R18.2
SOIL_TEMP3: JP2-DNP2.2, JP6.17, JP6.D4, R28.2
SOIL_TEMP4: JP2-DNP3.2, JP12.17, JP12.D4, R38.2
SOIL_TEMP5: JP2-DNP4.2, JP15.17, JP15.D4, R48.2
SOIL_TEMP6: JP2-DNP5.2, JP18.17, JP18.D4, R58.2
SOIL_TEMP7: JP2-DNP6.2, JP21.17, JP21.D4, R68.2
SOIL_TEMP8: JP2-DNP7.2, JP24.17, JP24.D4, R78.2
SOIL_TEMP9: JP2-DNP8.2, JP27.17, JP27.D4, R88.2
TXO: JP4-DNP.1, JP9.3, JP9.TX
TXO1: JP3.3, JP3.TX, JP4-DNP1.1
TXO2: JP4-DNP2.1, JP6.3, JP6.TX
TXO3: JP4-DNP3.1, JP12.3, JP12.TX
TXO4: JP4-DNP4.1, JP15.3, JP15.TX
TXO5: JP4-DNP5.1, JP18.3, JP18.TX
TXO6: JP4-DNP6.1, JP21.3, JP21.TX
TXO7: JP4-DNP7.1, JP24.3, JP24.TX
TXO8: JP4-DNP8.1, JP27.3, JP27.TX
VREG: C13.A, SJ2.3, U1.1, U1.3
VREG1: C15.A, SJ5.3, U4.1, U4.3
VREG2: C23.A, SJ8.3, U7.1, U7.3
VREG3: C31.A, SJ11.3, U10.1, U10.3
VREG4: C39.A, SJ14.3, U13.1, U13.3
VREG5: C47.A, SJ17.3, U16.1, U16.3
VREG6: C55.A, SJ20.3, U19.1, U19.3
VREG7: C63.A, SJ23.3, U22.1, U22.3
VREG8: C71.A, SJ26.3, U25.1, U25.3
WDIR: D7.A, D8.C, JP9.12, JP9.A0, R13.1, R17.2
WDIR1: D3.A, D4.C, JP3.12, JP3.A0, R2.2, R7.1
WDIR2: D15.A, D16.C, JP6.12, JP6.A0, R21.2, R24.1
WDIR3: D21.A, D22.C, JP12.12, JP12.A0, R31.2, R34.1
WDIR4: D27.A, D28.C, JP15.12, JP15.A0, R41.2, R44.1
WDIR5: D33.A, D34.C, JP18.12, JP18.A0, R51.2, R54.1
WDIR6: D39.A, D40.C, JP21.12, JP21.A0, R61.2, R64.1
WDIR7: D45.A, D46.C, JP24.12, JP24.A0, R71.2, R74.1
WDIR8: D51.A, D52.C, JP27.12, JP27.A0, R81.2, R84.1
WSPEED: D9.A, D10.C, JP9.16, JP9.D3, R14.1
WSPEED1: D1.A, D2.C, JP3.16, JP3.D3, R3.1
WSPEED2: D13.A, D14.C, JP6.16, JP6.D3, R22.1
WSPEED3: D19.A, D20.C, JP12.16, JP12.D3, R32.1
WSPEED4: D25.A, D26.C, JP15.16, JP15.D3, R42.1
WSPEED5: D31.A, D32.C, JP18.16, JP18.D3, R52.1
WSPEED6: D37.A, D38.C, JP21.16, JP21.D3, R62.1
WSPEED7: D43.A, D44.C, JP24.16, JP24.D3, R72.1
WSPEED8: D49.A, D50.C, JP27.16, JP27.D3, R82.1

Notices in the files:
parts and their libraries:
SparkFun-Aesthetics: Licensing: Creative Commons ShareAlike 4.0 International - https://creativecommons.org/licenses/by-sa/4.0
SparkFun-Aesthetics: Released under the Creative Commons Attribution Share-Alike 4.0 License
SparkFun-Aesthetics: https://creativecommons.org/licenses/by-sa/4.0
